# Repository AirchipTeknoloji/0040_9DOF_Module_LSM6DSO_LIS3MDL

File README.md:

# 0040_9DOF_Module_LSM6DSO_LIS3MDL

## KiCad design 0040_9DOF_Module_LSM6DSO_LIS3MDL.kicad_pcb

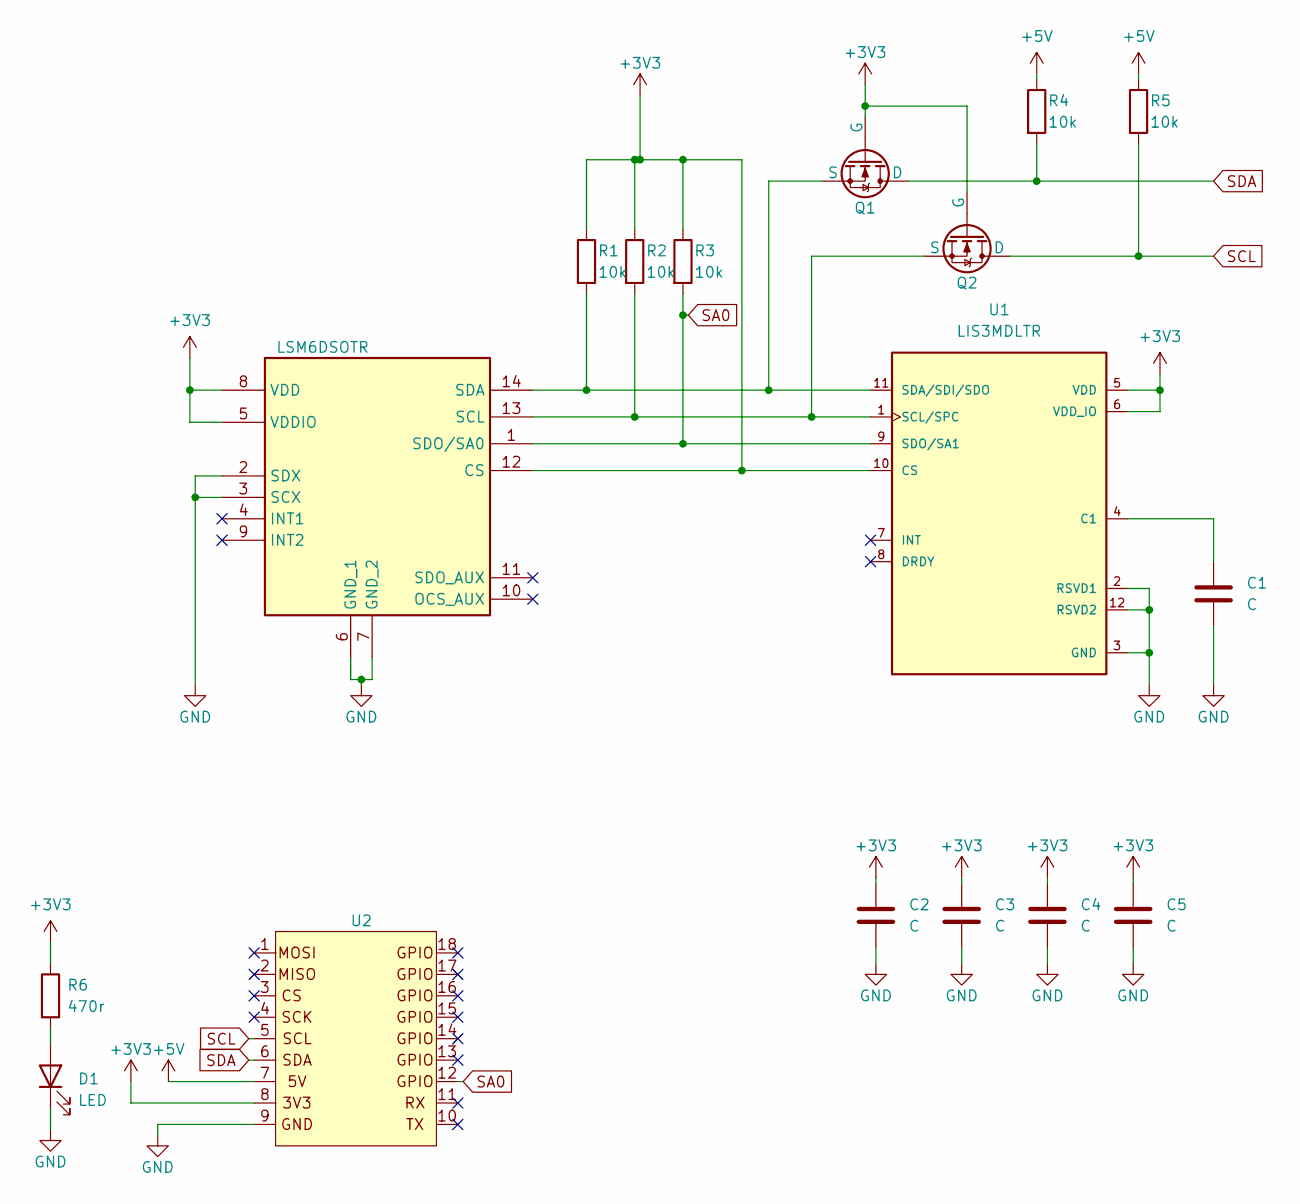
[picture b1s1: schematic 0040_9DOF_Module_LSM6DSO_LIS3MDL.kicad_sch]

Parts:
AC1: LSM6DSOTR; LGA-14_2.5X3X0.86_; Mouser Part Number 511-LSM6DSOTR
C1, C2, C3, C4, C5: C; C_0603_1608Metric
D1: LED; LED_0603_1608Metric
Q1, Q2: NMOS; SOT-23
R1, R2, R3, R4, R5: 10k; R_0603_1608Metric
R6: 470r; R_0603_1608Metric
U1: LIS3MDLTR; LGA12_2X2; PARTREV 6
U2: pin_header

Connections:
+3V3: AC1.5 (VDDIO), AC1.8 (VDD), AC1.12 (CS), C2.1, C3.1, C4.1, C5.1, Q1.2 (G), Q2.2 (G), R1.1, R2.1, R3.1, R6.1, U1.5 (VDD), U1.6 (VDD_IO), U1.10 (CS), U2.8
+5V: R4.1, R5.1, U2.7
GND: AC1.2 (SDX), AC1.3 (SCX), AC1.6 (GND_1), AC1.7 (GND_2), C1.2, C2.2, C3.2, C4.2, C5.2, D1.1 (K), U1.2 (RSVD1), U1.3 (GND), U1.12 (RSVD2), U2.9
unnamed: AC1.13 (SCL), Q2.3 (S), R2.2, U1.1 (SCL/SPC)
unnamed: AC1.14 (SDA), Q1.3 (S), R1.2, U1.11 (SDA/SDI/SDO)
unnamed: D1.2 (A), R6.2
unnamed: C1.1, U1.4 (C1)
SA0: AC1.1 (SDO/SA0), R3.2, U1.9 (SDO/SA1), U2.12
SCL: Q2.1 (D), R5.2, U2.5
SDA: Q1.1 (D), R4.2, U2.6

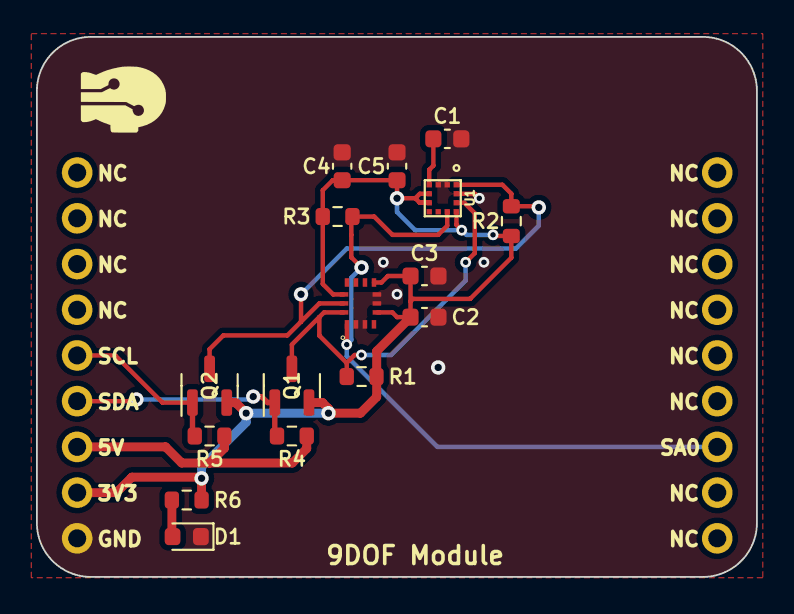
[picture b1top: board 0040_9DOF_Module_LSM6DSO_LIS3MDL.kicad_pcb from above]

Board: 2 copper layers, 40.0 x 30.0 mm, 17 parts (0 on the bottom side), 10 nets.
